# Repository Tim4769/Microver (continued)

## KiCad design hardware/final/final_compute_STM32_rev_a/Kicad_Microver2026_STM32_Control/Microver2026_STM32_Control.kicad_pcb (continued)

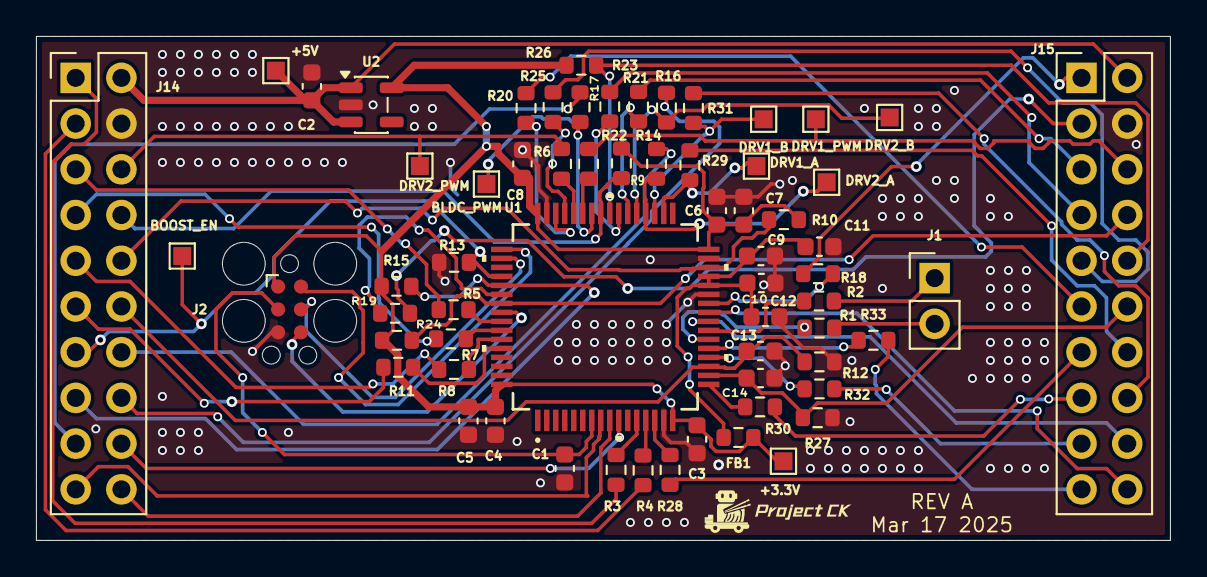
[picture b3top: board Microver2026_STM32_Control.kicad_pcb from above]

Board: 4 copper layers, 63.0 x 28.0 mm, 64 parts (0 on the bottom side), 71 nets.

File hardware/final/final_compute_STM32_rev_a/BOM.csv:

"Reference","Qty","Value","Footprint","JLCPCB part number"
"C1,C3,C4,C5,C7,C9,C11","7","100nF","Capacitor_SMD:C_0603_1608Metric","C14663"
"C2,C6,C8","3","4.7uF","Capacitor_SMD:C_0603_1608Metric","C19666"
"C10,C12","2","1uF","Capacitor_SMD:C_0603_1608Metric","C15849"
"C13,C14","2","10nF","Capacitor_SMD:C_0603_1608Metric","C57112"
"FB1","1","FerriteBead_Small","Resistor_SMD:R_0603_1608Metric","C14709"
"J1","1","Pi URAT","Connector_PinHeader_2.54mm:PinHeader_1x02_P2.54mm_Vertical","C492401"
"J2","1","TC2030","Connector:Tag-Connect_TC2030-IDC-FP_2x03_P1.27mm_Vertical",""
"J14","1","Left","Connector_PinHeader_2.54mm:PinHeader_2x10_P2.54mm_Vertical",""
"J15","1","Right","Connector_PinHeader_2.54mm:PinHeader_2x10_P2.54mm_Vertical",""
"R1,R2,R3,R4,R5,R7,R8,R11,R18,R19,R20,R21,R23,R25,R28,R30,R32,R33","18","100Ω","Resistor_SMD:R_0603_1608Metric","C22775"
"R6,R14,R16,R17,R22,R29,R31","7","1kΩ","Resistor_SMD:R_0603_1608Metric","C21190"
"R9,R10,R15,R24,R26","5","3.3kΩ","Resistor_SMD:R_0603_1608Metric","C22978"
"R12,R27","2","680Ω","Resistor_SMD:R_0603_1608Metric","C23228"
"R13","1","10kΩ","Resistor_SMD:R_0603_1608Metric","C25804"
"TP1","1","+5V","TestPoint:TestPoint_Pad_1.0x1.0mm",""
"TP2","1","+3.3V","TestPoint:TestPoint_Pad_1.0x1.0mm",""
"TP3","1","BLDC_PWM","TestPoint:TestPoint_Pad_1.0x1.0mm",""
"TP4","1","DRV1_A","TestPoint:TestPoint_Pad_1.0x1.0mm",""
"TP5","1","DRV1_B","TestPoint:TestPoint_Pad_1.0x1.0mm",""
"TP6","1","DRV2_A","TestPoint:TestPoint_Pad_1.0x1.0mm",""
"TP7","1","DRV1_PWM","TestPoint:TestPoint_Pad_1.0x1.0mm",""
"TP8","1","DRV2_B","TestPoint:TestPoint_Pad_1.0x1.0mm",""
"TP12","1","DRV2_PWM","TestPoint:TestPoint_Pad_1.0x1.0mm",""
"TP15","1","BOOST_EN","TestPoint:TestPoint_Pad_1.0x1.0mm",""
"U1","1","STM32G473RCT6","STM32_Footprint_Library:LQFP64-10x10mm","C529361"
"U2","1","MIC5365-3.3YD5","Package_TO_SOT_SMD:SOT-23-5","C626098"

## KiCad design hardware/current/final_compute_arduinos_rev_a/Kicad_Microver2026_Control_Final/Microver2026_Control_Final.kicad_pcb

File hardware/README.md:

# Hardware Index

Use this index to avoid opening stale revisions by accident.

## Start here
- `final/README.md` - Latest board revisions (active work only).

## Historical revisions
- `archive/README.md` - Archived revisions and legacy boards.

## Important after folder moves
- KiCad output paths in project files may still point to old folder locations.
- After moving a board revision, update KiCad plot and export paths (Gerber, drill, BOM, CPL) before regenerating manufacturing outputs.

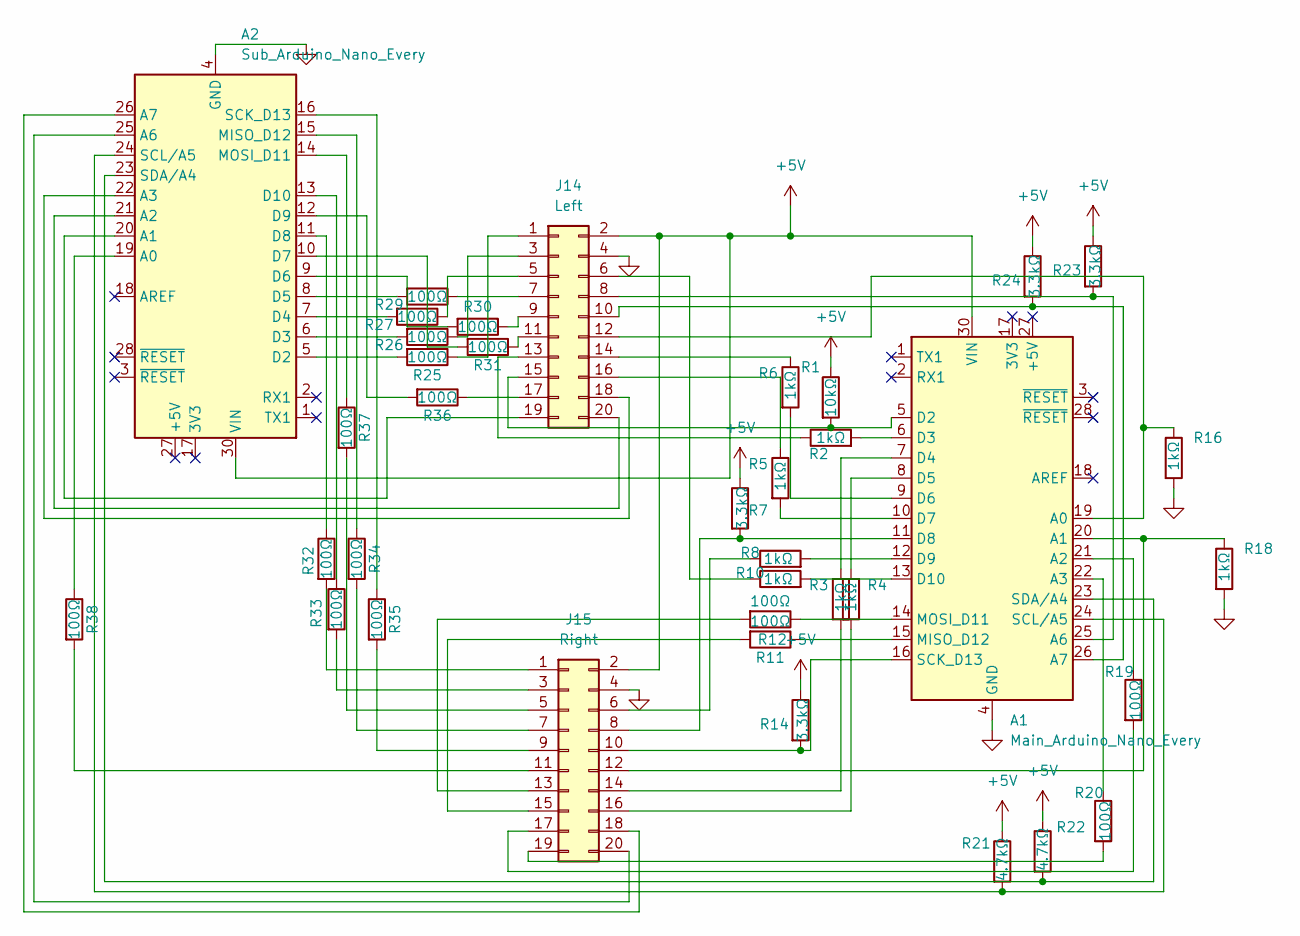
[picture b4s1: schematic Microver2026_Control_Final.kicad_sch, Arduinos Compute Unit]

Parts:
A1: Main_Arduino_Nano_Every; Arduino_Nano
A2: Sub_Arduino_Nano_Every; Arduino_Nano
J14: Left; PinHeader_2x10_P2.54mm_Vertical
J15: Right; PinHeader_2x10_P2.54mm_Vertical
R1: 10kΩ; R_0603_1608Metric; JLCPCB part number C25804
R2, R3, R4, R5, R6, R8, R10, R16, R18: 1kΩ; R_0603_1608Metric; JLCPCB part number C21190
R7, R14, R23, R24: 3.3kΩ; R_0603_1608Metric; JLCPCB part number C22978
R11, R12, R19, R20, R25, R26, R27, R29, R30, R31, R32, R33, R34, R35, R36, R37, R38: 100Ω; R_0603_1608Metric; JLCPCB part number C22775
R21, R22: 4.7kΩ; R_0603_1608Metric; JLCPCB part number C23162

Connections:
+5V: A1.30 (VIN), A2.30 (VIN), J14.2 (Pin_1b), J15.2 (Pin_1b), R1.1, R7.1, R14.1, R21.1, R22.1, R23.1, R24.1
GND: A1.4 (GND), A1.29 (GND), A2.4 (GND), A2.29 (GND), J14.4 (Pin_2b), J15.4 (Pin_2b), R16.2, R18.2
unnamed: A1.19 (A0), J14.12 (Pin_6b), R16.1
unnamed: A1.20 (A1), J15.12 (Pin_6b), R18.1
unnamed: A1.21 (A2), R19.1
unnamed: A1.22 (A3), R20.1
unnamed: A1.25 (A6), J14.8 (Pin_4b), R23.2
unnamed: A1.26 (A7), J14.10 (Pin_5b), R24.2
unnamed: A1.5 (D2), J14.15 (Pin_8a), R1.2
unnamed: A1.6 (D3), R2.2
unnamed: A1.7 (D4), R3.1
unnamed: A1.8 (D5), R4.1
unnamed: A1.9 (D6), R6.2
unnamed: A1.10 (D7), R5.2
unnamed: A1.11 (D8), J15.8 (Pin_4b), R7.2
unnamed: A1.12 (D9), R8.2
unnamed: A1.13 (D10), R10.2
unnamed: A1.15 (MISO_D12), R12.1
unnamed: A1.14 (MOSI_D11), R11.1
unnamed: A1.16 (SCK_D13), J15.10 (Pin_5b), R14.2
unnamed: A1.24 (SCL/A5), A2.24 (SCL/A5), R21.2
unnamed: A1.23 (SDA/A4), A2.23 (SDA/A4), R22.2
unnamed: A2.19 (A0), R38.1
unnamed: A2.20 (A1), J14.19 (Pin_10a)
unnamed: A2.21 (A2), J14.20 (Pin_10b)
unnamed: A2.22 (A3), J14.18 (Pin_9b)
unnamed: A2.25 (A6), J15.20 (Pin_10b)
unnamed: A2.26 (A7), J15.18 (Pin_9b)
unnamed: A2.5 (D2), R25.2
unnamed: A2.6 (D3), R26.2
unnamed: A2.7 (D4), R27.2
unnamed: A2.8 (D5), R29.2
unnamed: A2.9 (D6), R30.2
unnamed: A2.10 (D7), R31.2
unnamed: A2.11 (D8), R32.1
unnamed: A2.12 (D9), R36.2
unnamed: A2.13 (D10), R33.1
unnamed: A2.15 (MISO_D12), R34.1
unnamed: A2.14 (MOSI_D11), R37.1
unnamed: A2.16 (SCK_D13), R35.1
unnamed: J14.1 (Pin_1a), R25.1
unnamed: J14.3 (Pin_2a), R26.1
unnamed: J14.5 (Pin_3a), R27.1
unnamed: J14.6 (Pin_3b), R10.1
unnamed: J14.7 (Pin_4a), R29.1
unnamed: J14.9 (Pin_5a), R30.1
unnamed: J14.11 (Pin_6a), R31.1
unnamed: J14.13 (Pin_7a), R2.1
unnamed: J14.14 (Pin_7b), R6.1
unnamed: J14.16 (Pin_8b), R5.1
unnamed: J14.17 (Pin_9a), R36.1
unnamed: J15.1 (Pin_1a), R32.2
unnamed: J15.3 (Pin_2a), R33.2
unnamed: J15.5 (Pin_3a), R37.2
unnamed: J15.6 (Pin_3b), R8.1
unnamed: J15.7 (Pin_4a), R34.2
unnamed: J15.9 (Pin_5a), R35.2
unnamed: J15.11 (Pin_6a), R38.2
unnamed: J15.13 (Pin_7a), R11.2
unnamed: J15.14 (Pin_7b), R3.2
unnamed: J15.15 (Pin_8a), R12.2
unnamed: J15.16 (Pin_8b), R4.2
unnamed: J15.17 (Pin_9a), R19.2
unnamed: J15.19 (Pin_10a), R20.2

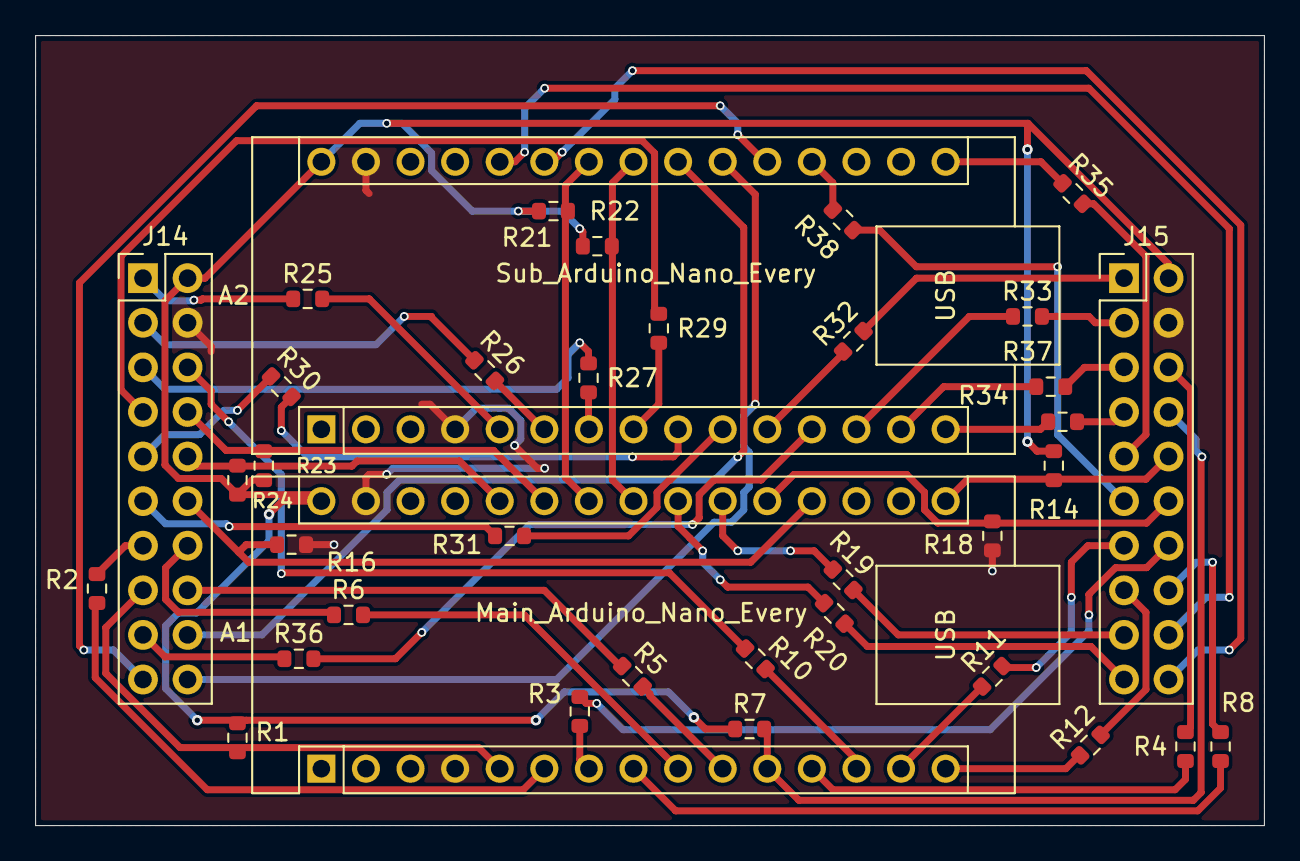
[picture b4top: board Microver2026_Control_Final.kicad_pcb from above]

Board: 4 copper layers, 70.0 x 45.0 mm, 37 parts (0 on the bottom side), 64 nets.

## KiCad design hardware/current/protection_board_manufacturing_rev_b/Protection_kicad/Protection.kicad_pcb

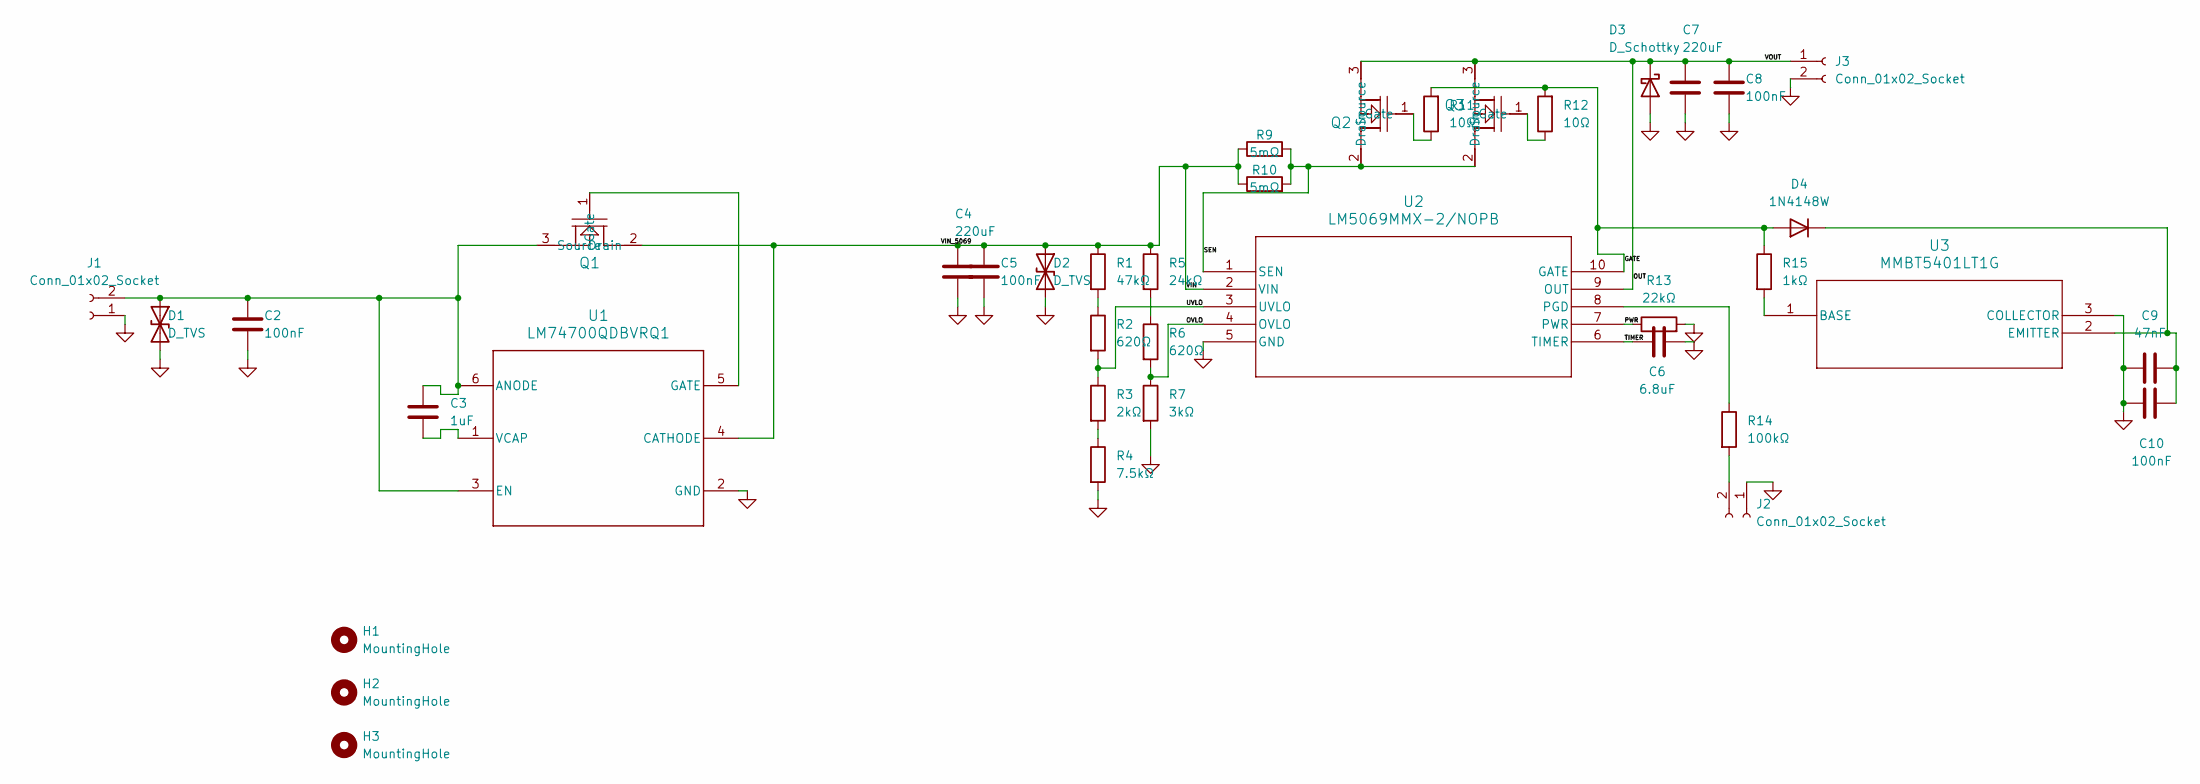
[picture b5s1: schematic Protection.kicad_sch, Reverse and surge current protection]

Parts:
C2, C5, C8, C10: 100nF; C_0603_1608Metric
C3: 1uF; C_0805_2012Metric
C4, C7: 220uF; CP_Radial_D10.0mm_P5.00mm
C6: 6.8uF; C_0603_1608Metric
C9: 47nF; C_0603_1608Metric
D1, D2: D_TVS; D_SMB
D3: D_Schottky; D_SMC
D4: 1N4148W; D_SOD-123
H1, H2, H3: MountingHole; MountingHole_3.2mm_M3
J1, J3: Conn_01x02_Socket; TerminalBlock_MaiXu_MX126-5.0-02P_1x02_P5.00mm
J2: Conn_01x02_Socket; PinHeader_1x02_P2.54mm_Vertical
Q1, Q2, Q3: CSD19536KTT; KTT0002A
R1: 47kΩ; R_0603_1608Metric
R2, R6: 620Ω; R_0603_1608Metric
R3: 2kΩ; R_0603_1608Metric
R4: 7.5kΩ; R_0603_1608Metric
R5: 24kΩ; R_0603_1608Metric
R7: 3kΩ; R_0603_1608Metric
R9, R10: 5mΩ; R_2512_6332Metric
R11, R12: 10Ω; R_0603_1608Metric
R13: 22kΩ; R_0603_1608Metric
R14: 100kΩ; R_0603_1608Metric
R15: 1kΩ; R_0603_1608Metric
U1: LM74700QDBVRQ1; DBV0006A_N
U2: LM5069MMX-2/NOPB; MUB10A
U3: MMBT5401LT1G; SOT-23-3_1P4X3P040_ONS

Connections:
/GATE: D4.2 (A), R11.2, R12.2, R15.1, U2.10 (GATE)
/OUT: C7.1, C8.1, D3.1 (K), J3.1, Q2.3 (Source), Q3.3 (Source), U2.9 (OUT)
/OVLO: R6.2, R7.1, U2.4 (OVLO)
/PWR: R13.1, U2.7 (PWR)
/SEN: Q2.2 (Drain), Q3.2 (Drain), R9.2, R10.2, U2.1 (SEN)
/TIMER: C6.1, U2.6 (TIMER)
/UVLO: R2.2, R3.1, U2.3 (UVLO)
/VIN: C4.1, C5.1, D2.1 (A1), Q1.2 (Drain), R1.1, R5.1, R9.1, R10.1, U1.4 (CATHODE), U2.2 (VIN)
GND: C2.2, C4.2, C5.2, C6.2, C7.2, C8.2, C9.1, C10.1, D1.2 (A2), D2.2 (A2), D3.2 (A), J1.1, J2.1, J3.2, R4.2, R7.2, R13.2, U1.2 (GND), U2.5 (GND), U3.3 (COLLECTOR)
unnamed: C2.1, C3.1, D1.1 (A1), J1.2, Q1.3 (Source), U1.3 (EN), U1.6 (ANODE)
unnamed: C9.2, C10.2, D4.1 (K), U3.2 (EMITTER)
unnamed: J2.2, R14.2
unnamed: Q1.1 (Gate), U1.5 (GATE)
unnamed: Q2.1 (Gate), R11.1
unnamed: Q3.1 (Gate), R12.1
unnamed: R1.2, R2.1
unnamed: R3.2, R4.1
unnamed: R5.2, R6.1
unnamed: C3.2, U1.1 (VCAP)
unnamed: R14.1, U2.8 (PGD)
unnamed: R15.2, U3.1 (BASE)

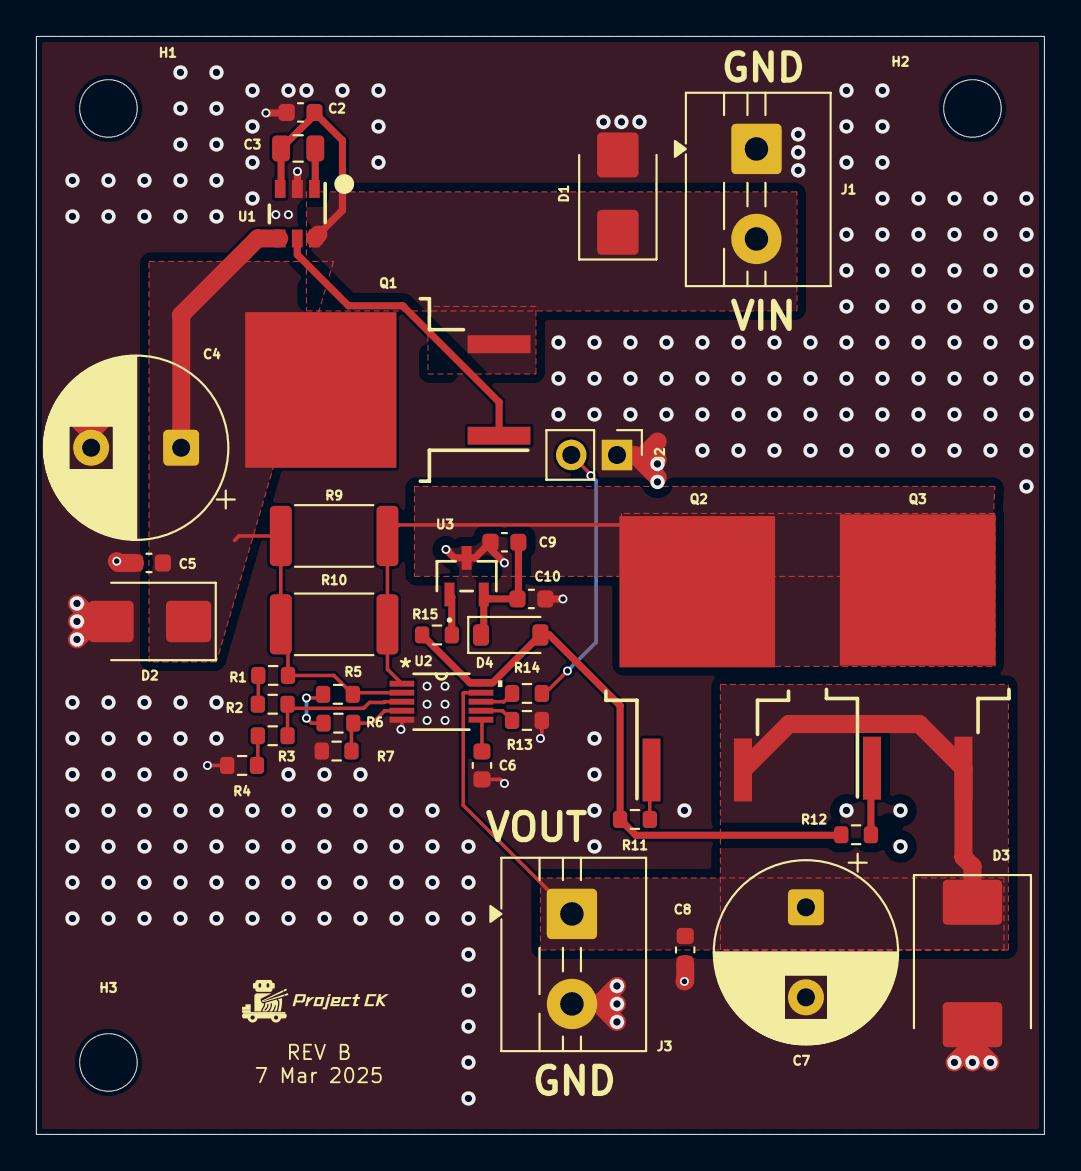
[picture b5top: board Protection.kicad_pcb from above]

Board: 4 copper layers, 56.0 x 61.0 mm, 39 parts (0 on the bottom side), 21 nets.

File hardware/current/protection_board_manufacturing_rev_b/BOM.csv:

"Reference","Qty","Value","Footprint","Datasheet","JPCPCB part number"
"C1,C4,C7","3","220uF","Capacitor_THT:CP_Radial_D10.0mm_P5.00mm","~","C106670"
"C2,C5,C8,C10","4","100nF","Capacitor_SMD:C_0603_1608Metric","~","C14663"
"C3","1","1uF","Capacitor_SMD:C_0805_2012Metric","~","C28323"
"C6","1","6.8uF","Capacitor_SMD:C_0603_1608Metric","~","C338096"
"C9","1","47nF","Capacitor_SMD:C_0603_1608Metric","~","C1622"
"D1,D2","2","D_TVS","Diode_SMD:D_SMB","~","C19077586"
"D3","1","D_Schottky","Diode_SMD:D_SMC","~","C134457"
"D4","1","1N4148W","Diode_SMD:D_SOD-123","https://www.vishay.com/docs/85748/1n4148w.pdf","C7420318"
"J1,J3","2","Conn_01x02_Socket","TerminalBlock:TerminalBlock_MaiXu_MX126-5.0-02P_1x02_P5.00mm","~",""
"J2","1","Conn_01x02_Socket","Connector_PinHeader_2.54mm:PinHeader_1x02_P2.54mm_Vertical","~",""
"Q1,Q2,Q3","3","CSD19536KTT","KTT0002A","https://www.ti.com/lit/gpn/csd19536ktt","C2687963"
"R1","1","47kΩ","Resistor_SMD:R_0603_1608Metric","~","C25819"
"R2,R6","2","620Ω","Resistor_SMD:R_0603_1608Metric","~","C23220"
"R3","1","2kΩ","Resistor_SMD:R_0603_1608Metric","~","C22975"
"R4","1","7.5kΩ","Resistor_SMD:R_0603_1608Metric","~","C23234"
"R5","1","24kΩ","Resistor_SMD:R_0603_1608Metric","~","C23352"
"R7","1","3kΩ","Resistor_SMD:R_0603_1608Metric","~","C4211"
"R8","1","33Ω","Resistor_SMD:R_0603_1608Metric","~","C23140"
"R9,R10","2","5mΩ","Resistor_SMD:R_2512_6332Metric","~","C108931"
"R11,R12","2","10Ω","Resistor_SMD:R_0603_1608Metric","~","C22859"
"R13","1","22kΩ","Resistor_SMD:R_0603_1608Metric","~","C31850"
"R14","1","100kΩ","Resistor_SMD:R_0603_1608Metric","~","C25803"
"R15","1","1kΩ","Resistor_SMD:R_0603_1608Metric","~","C21190"
"U1","1","LM74700QDBVRQ1","DBV0006A_N","https://www.ti.com/lit/gpn/lm74700-q1","C2941042"
"U2","1","LM5069MMX-2/NOPB","MUB10A","https://www.ti.com/lit/gpn/lm5069","C2653582"
"U3","1","MMBT5401LT1G","SOT-23-3_1P4X3P040_ONS","MMBT5401LT1G","C21488"

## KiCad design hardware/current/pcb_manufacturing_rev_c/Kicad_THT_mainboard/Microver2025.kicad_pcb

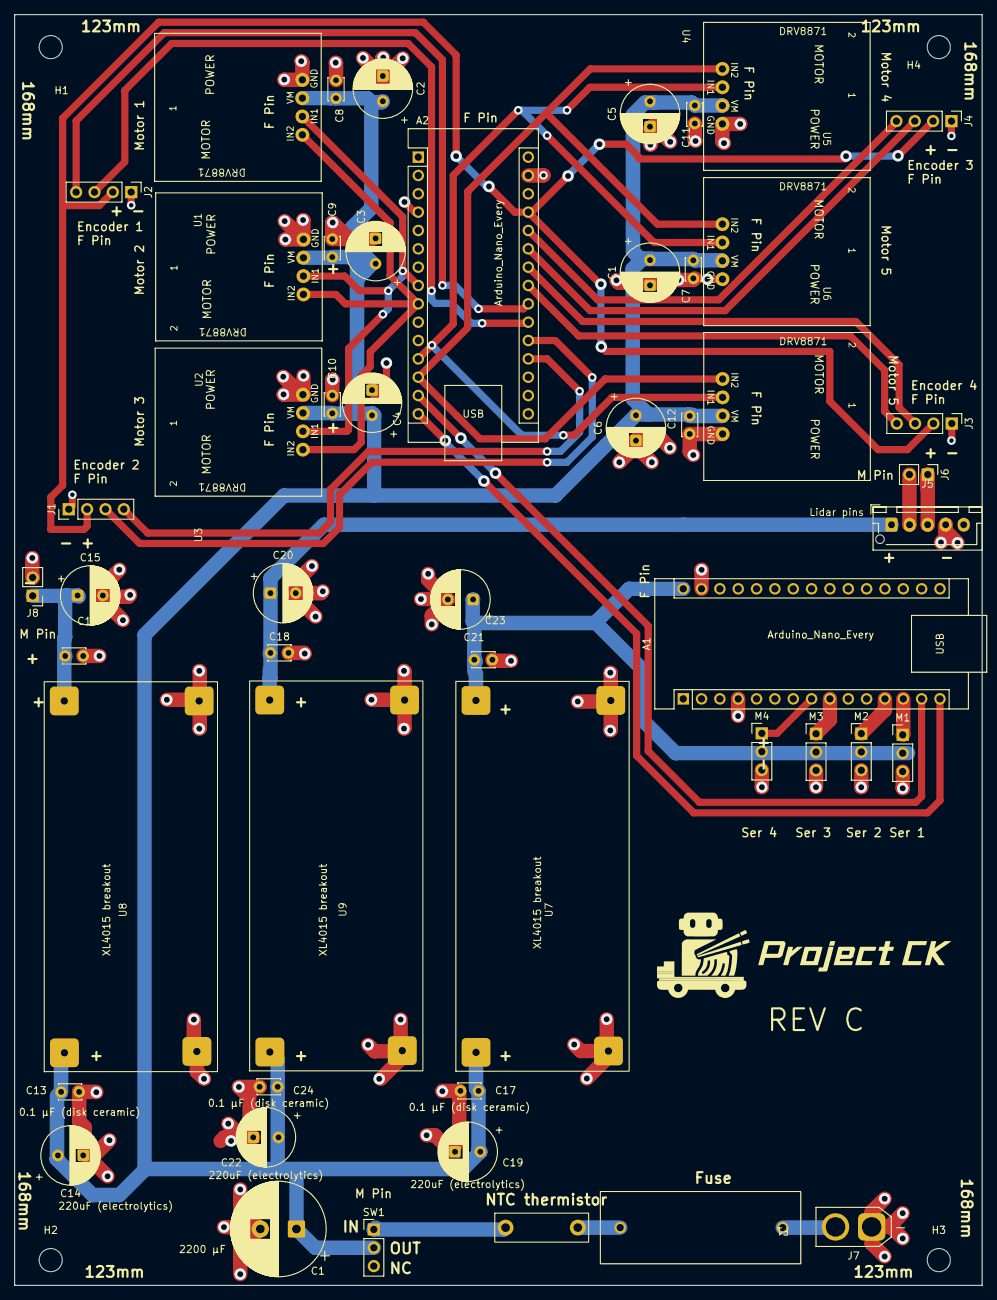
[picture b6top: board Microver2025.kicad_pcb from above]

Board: 4 copper layers, 134.0 x 176.0 mm, 55 parts (0 on the bottom side), 23 nets.

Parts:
A1, A2: Arduino_Nano_Every; Arduino_Nano
C1: 2200 µF; CP_Radial_D13.0mm_P5.00mm
C1#2, C2, C3, C4, C5, C6, C14, C19, C22: 220uF (electrolytics); Marking reversed CP_Radial_D8.0mm_P3.50mm
C7, C8, C9, C10, C11, C12, C13, C16, C17, C18, C23, C24: 0.1 µF (disk ceramic); C_Disc_D3.0mm_W2.0mm_P2.50mm
C15, C20, C21: 220uF (electrolytics); CP_Radial_D8.0mm_P3.50mm
F1: Fuse; Fuse PTF-77
H1, H2, H3, H4: MountingHole; MountingHole_3.2mm_M3
J1, J2, J3, J4: Encoder pins; PinHeader_1x04_P2.54mm_Vertical
J5: Lidar pins; JST_XH_B5B-XH-AM_1x05_P2.50mm_Vertical
J6: Pi 5 TX and RX UART0 (PL011); PinHeader_1x02_P2.54mm_Vertical
J7: Power input connect from battery; AMASS_XT30U-M_1x02_P5.0mm_Vertical
J8: Pi power pins; PinHeader_1x02_P2.54mm_Vertical
M1, M2, M3, M4: Motor_Servo (MG996R); PinHeader_1x03_P2.54mm_Vertical
SW1: SW_SPDT; PinHeader_1x03_P2.54mm_Vertical
TH1: Thermistor_NTC; NTC thermistor Microver
U1, U2, U3, U4, U5, U6: DRV8871_breakout; DRV8871 breakout board
U7, U8, U9: XL4015 breakout; XL4015 breakout board

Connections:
+18V: C1.1, C1#2.2, C2.2, C3.2, C4.2, C5.2, C6.2, C7.2, C8.2, C9.2, C10.2, C11.2, C12.2, C13.2, C14.2, C17.2, C19.2, C22.2, C24.2, F1.1, F1.2, J7.2, SW1.1 (A), SW1.2 (B), TH1.1, TH1.2, U1.4 (VM), U2.4 (VM), U3.4 (VM), U4.4 (VM), U5.4 (VM), U6.4 (VM), U7.1 (IN+), U8.1 (IN+), U9.1 (IN+)
/5V: A1.30 (VIN), A2.27 (+5V), C15.1, C16.1, C18.1, C20.1, C21.1, C23.1, J1.2, J2.2, J3.2, J4.2, J5.1, J8.1, M1.2 (+), M2.2 (+), M3.2 (+), M4.2 (+), U7.3 (OUT+), U8.3 (OUT+), U9.3 (OUT+)
/DIGI_1_1: A2.21 (A2), J2.3
/DIGI_1_2: A2.22 (A3), J2.4
/DIGI_2_1: A2.20 (A1), J1.3
/DIGI_2_2: A2.19 (A0), J1.4
/DIGI_3_1: A2.25 (A6), J4.3
/DIGI_3_2: A2.26 (A7), J4.4
/DIGI_4_1: A2.24 (SCL/A5), J3.3
/DIGI_4_2: A2.23 (SDA/A4), J3.4
/PWM_M1_1: A2.8 (D5), U1.3 (IN1), U2.3 (IN1), U3.3 (IN1)
/PWM_M1_2: A2.9 (D6), U1.2 (IN2), U2.2 (IN2), U3.2 (IN2)
/PWM_M4_1: A2.12 (D9), U4.3 (IN1), U5.3 (IN1), U6.3 (IN1)
/PWM_M4_2: A2.13 (D10), U4.2 (IN2), U5.2 (IN2), U6.2 (IN2)
/PWM_SER1: A1.13 (D10), M1.1 (PWM)
/PWM_SER2: A1.12 (D9), M2.1 (PWM)
/PWM_SER3: A1.9 (D6), M3.1 (PWM)
/PWM_SER4: A1.8 (D5), M4.1 (PWM)
/URAT_MI: A1.14 (MOSI), A2.14 (MOSI)
/URAT_MO: A1.15 (MISO), A2.15 (MISO)
/URAT_PI_1: J5.3, J6.1
/URAT_PI_2: J5.2, J6.2
GND: A1.4 (GND), A1.29 (GND), A2.4 (GND), A2.29 (GND), C1.2, C1#2.1, C2.1, C3.1, C4.1, C5.1, C6.1, C7.1, C8.1, C9.1, C10.1, C11.1, C12.1, C13.1, C14.1, C15.2, C16.2, C17.1, C18.2, C19.1, C20.2, C21.2, C22.1, C23.2, C24.1, J1.1, J2.1, J3.1, J4.1, J5.4, J7.1, J8.2, M1.3 (-), M2.3 (-), M3.3 (-), M4.3 (-), U1.1 (GND), U2.1 (GND), U3.1 (GND), U4.1 (GND), U5.1 (GND), U6.1 (GND), U7.2 (IN-), U7.4 (OUT-), U8.2 (IN-), U8.4 (OUT-), U9.2 (IN-), U9.4 (OUT-)

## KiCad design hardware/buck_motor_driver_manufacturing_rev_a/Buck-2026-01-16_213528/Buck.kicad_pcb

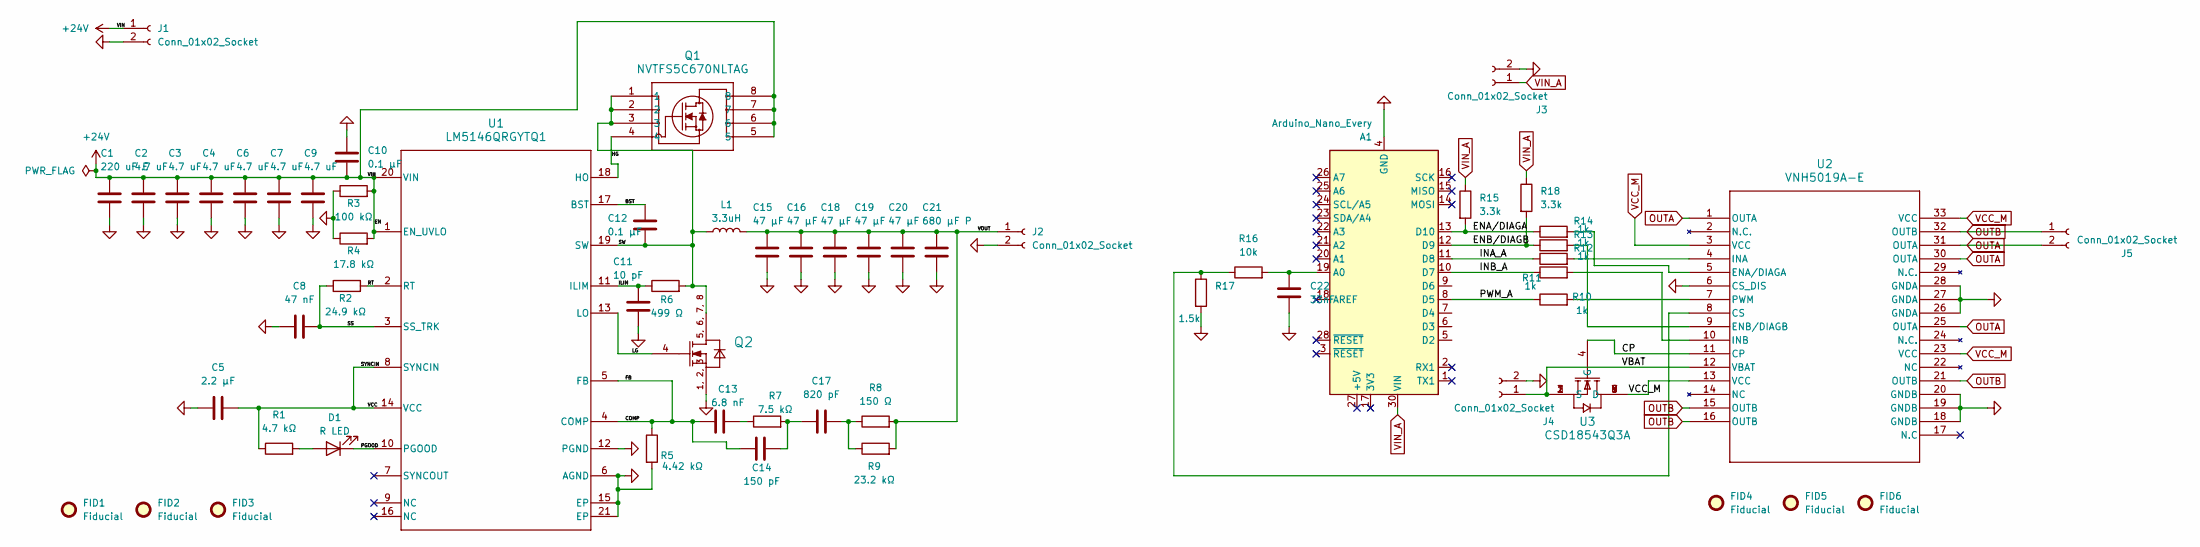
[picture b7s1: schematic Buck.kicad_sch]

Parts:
A1: Arduino_Nano_Every; Arduino_Nano
C1: 220 uF E; CP_Elec_4x5.4; JLCPCB Part Number C116389
C2, C3, C4, C6, C7, C9: 4.7 uF; C_1206_3216Metric; JLCPCB Part Number C51205
C5: 2.2 μF; C_0603_1608Metric; JLCPCB Part Number C43922
C8: 47 nF; C_0402_1005Metric; JLCPCB Part Number C307434
C10, C12: 0.1 μF; C_0603_1608Metric; JLCPCB Part Number C14663
C11: 10 pF; C_0402_1005Metric; JLCPCB Part Number C1845716
C13: 6.8 nF; C_0603_1608Metric; JLCPCB Part Number C107097
C14: 150 pF; C_0603_1608Metric; JLCPCB Part Number C1594
C15, C16, C18, C19, C20: 47 μF; C_1210_3225Metric; JLCPCB Part Number C5440143
C17: 820 pF; C_0603_1608Metric; JLCPCB Part Number C1632
C21: 680 µF P; MA35V680M10X13; JLCPCB Part Number C48971043
C22: 33nF; C_0603_1608Metric; JLCPCB Part Number C21117
D1: R LED; LED_0402_1005Metric; JLCPCB Part Number C510301
FID1, FID2, FID3, FID4, FID5, FID6: Fiducial; Fiducial_1mm_Mask2mm
J1, J2, J3, J4, J5: Conn_01x02_Socket; TerminalBlock_MaiXu_MX126-5.0-02P_1x02_P5.00mm; JLCPCB Part Number C8269
L1: 3.3uH; MS1770-3R3M; JLCPCB Part Number C18337521
Q1: NVTFS5C670NLTAG; WDFN8_511AB_ONS; JLCPCB Part Number C900529
Q2: BSC014N06NS; INF-PG-TDSON-8-FL; ManufacturerPartNumber BSC014N06NS; JLCPCB Part Number C113391
R1: 4.7 kΩ; R_0402_1005Metric; JLCPCB Part Number C25900
R2: 24.9 kΩ; R_0603_1608Metric; JLCPCB Part Number C25962
R3: 100 kΩ; R_0603_1608Metric; JLCPCB Part Number C25803
R4: 17.8 kΩ; R_0603_1608Metric; JLCPCB Part Number C2933161
R5: 4.42 kΩ; R_0805_2012Metric; JLCPCB Part Number C2960870
R6: 499 Ω; R_0603_1608Metric; JLCPCB Part Number C23065
R7: 7.5 kΩ; R_0603_1608Metric; JLCPCB Part Number C23234
R8: 150 Ω; R_0603_1608Metric; JLCPCB Part Number C22808
R9: 23.2 kΩ; R_0603_1608Metric; JLCPCB Part Number C23346
R10, R11, R12, R13, R14: 1k; R_0603_1608Metric; JLCPCB Part Number C21190
R15, R18: 3.3k; R_0603_1608Metric; JLCPCB Part Number C22978
R16: 10k; R_0603_1608Metric; JLCPCB Part Number C25804
R17: 1.5k; R_0603_1608Metric; JLCPCB Part Number C22843
U1: LM5146QRGYTQ1; RGY0020B; JLCPCB Part Number C2876733
U2: VNH5019A-E; SOIC_5019A-E_STM; JLCPCB Part Number C2653552
U3: CSD18543Q3A; DNH0008A; JLCPCB Part Number C840100

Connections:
+24V: C1.1, C2.1, C3.1, C4.1, C6.1, C7.1, C9.1, C10.2, J1.1, Q1.5, Q1.6, Q1.7, Q1.8, R3.2, R4.2, U1.1 (EN_UVLO), U1.20 (VIN)
/BST: C12.1, U1.17 (BST)
/COMP: C13.1, C14.1, R5.1, U1.4 (COMP), U1.5 (FB)
/CP: U2.11 (CP), U3.4 (G)
/ENA/DIAGA: A1.13 (D10), R14.1, R15.2
/ENB/DIAGB: A1.12 (D9), R13.1, R18.2
/HG: Q1.4, U1.18 (HO)
/ILIM: C11.1, R6.1, U1.11 (ILIM)
/INA_A: A1.11 (D8), R12.1
/INB_A: A1.10 (D7), R11.1
/LG: Q2.4 (GATE), U1.13 (LO)
/PGOOD: D1.1 (K), U1.10 (PGOOD)
/PWM_A: A1.8 (D5), R10.1
/RT: R2.2, U1.2 (RT)
/SS: C8.2, R2.1, U1.3 (SS_TRK)
/SW: C12.2, L1.1, Q1.1, Q1.2, Q1.3, Q2.5 (DRAIN), Q2.6 (DRAIN), Q2.7 (DRAIN), Q2.8 (DRAIN), R6.2, U1.19 (SW)
/SYNCIN: C5.2, R1.1, U1.8 (SYNCIN), U1.14 (VCC)
/VBAT: J4.1, U2.12 (VBAT), U3.1 (S), U3.2 (S), U3.3 (S)
/VOUT: C15.1, C16.1, C18.1, C19.1, C20.1, C21.1, J2.1, L1.2, R8.2, R9.2
GND: A1.4 (GND), A1.29 (GND), C1.2, C2.2, C3.2, C4.2, C5.1, C6.2, C7.2, C8.1, C9.2, C10.1, C11.2, C15.2, C16.2, C18.2, C19.2, C20.2, C21.2, C22.2, J1.2, J2.2, J3.2, J4.2, Q2.1 (SOURCE), Q2.2 (SOURCE), Q2.3 (SOURCE), R3.1, R4.1, R5.2, R17.2, U1.6 (AGND), U1.12 (PGND), U1.15 (EP), U1.21 (EP), U1.V, U2.6 (CS_DIS), U2.18 (GNDB), U2.19 (GNDB), U2.20 (GNDB), U2.26 (GNDA), U2.27 (GNDA), U2.28 (GNDA)
unnamed: A1.19 (A0), C22.1, R16.2
unnamed: C13.2, R7.1
unnamed: C14.2, C17.1, R7.2
unnamed: C17.2, R8.1, R9.1
unnamed: D1.2 (A), R1.2
unnamed: R16.1, R17.1, U2.8 (CS)
unnamed: R14.2, U2.5 (ENA/DIAGA)
unnamed: R13.2, U2.9 (ENB/DIAGB)
unnamed: R12.2, U2.4 (INA)
unnamed: R11.2, U2.10 (INB)
unnamed: R10.2, U2.7 (PWM)
OUTA: J5.2, U2.1 (OUTA), U2.25 (OUTA), U2.30 (OUTA), U2.31 (OUTA)
OUTB: J5.1, U2.15 (OUTB), U2.16 (OUTB), U2.21 (OUTB), U2.32 (OUTB)
VCC_M: U2.3 (VCC), U2.13 (VCC), U2.23 (VCC), U2.33 (VCC), U3.5 (D), U3.6 (D), U3.7 (D), U3.8 (D), U3.9 (D), U3.V
VIN_A: A1.30 (VIN), J3.1, R15.1, R18.1

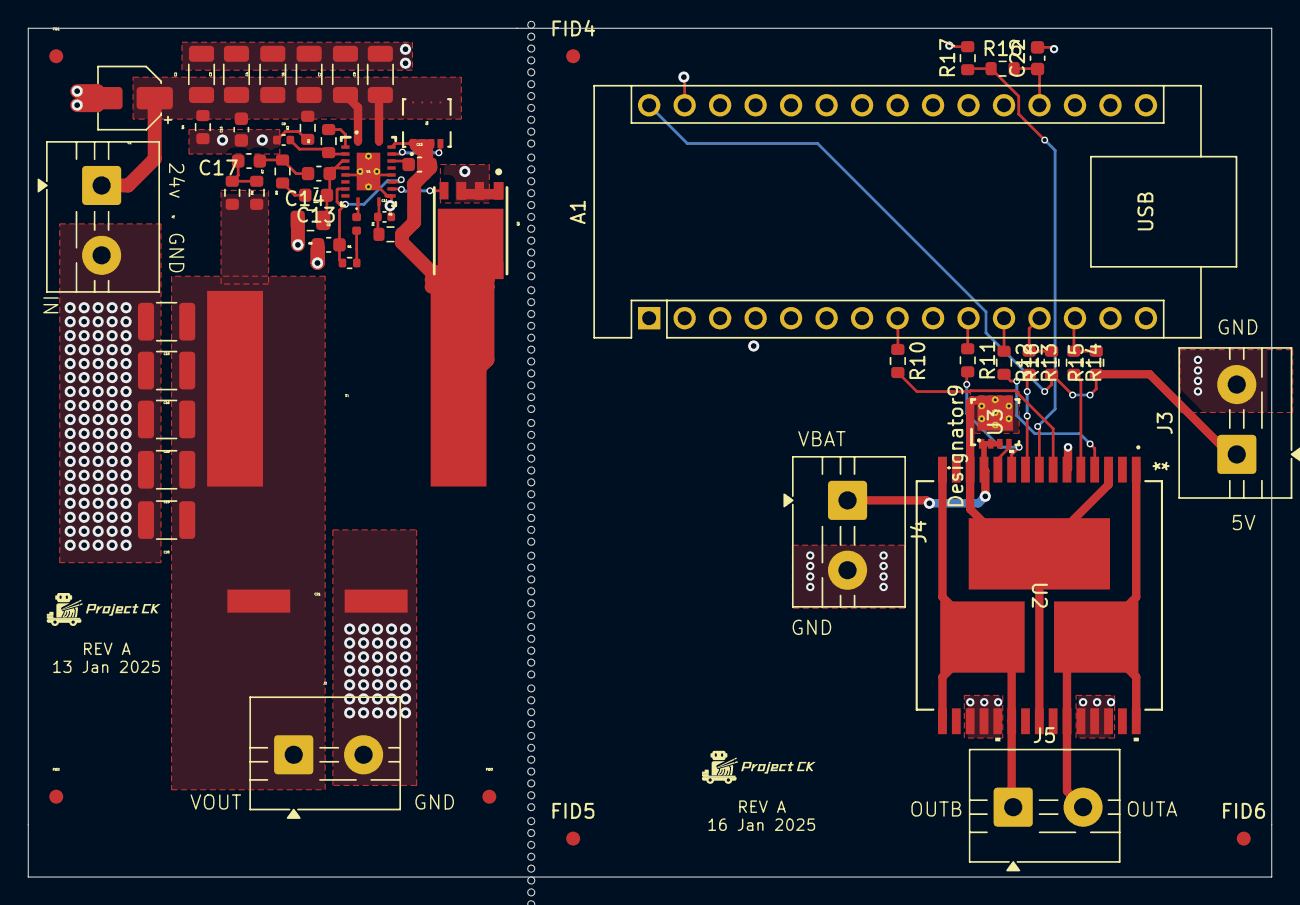
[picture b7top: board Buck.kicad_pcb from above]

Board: 4 copper layers, 89.0 x 60.8 mm, 59 parts (0 on the bottom side), 35 nets.

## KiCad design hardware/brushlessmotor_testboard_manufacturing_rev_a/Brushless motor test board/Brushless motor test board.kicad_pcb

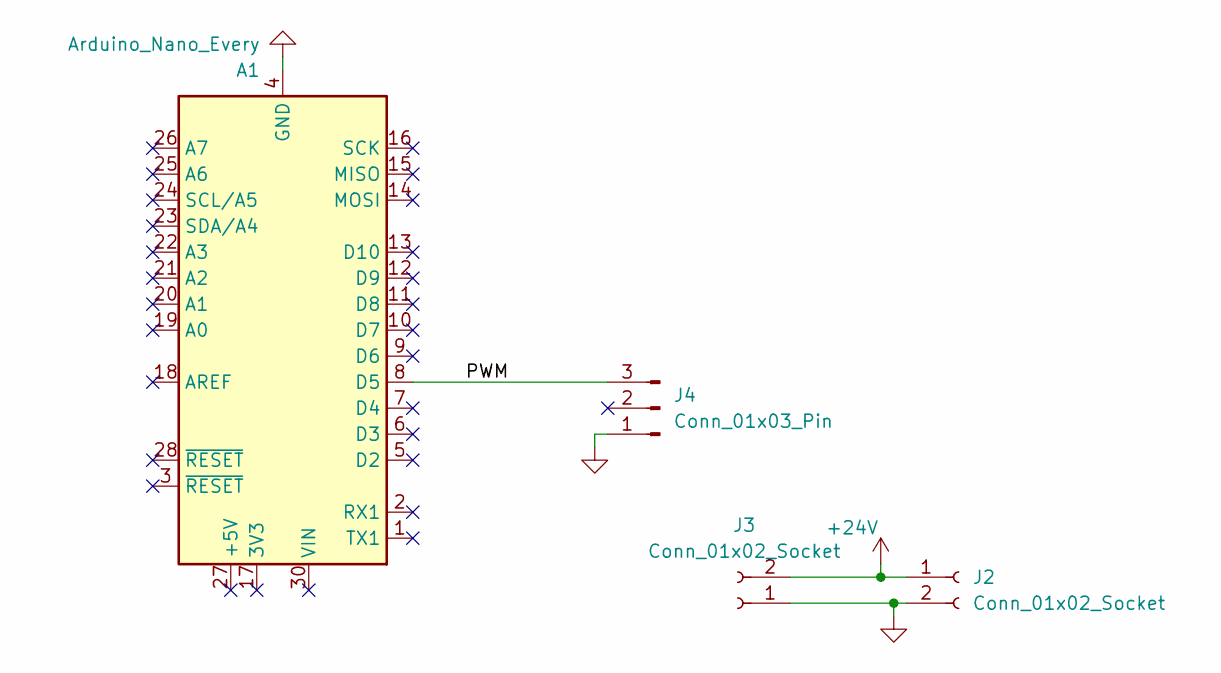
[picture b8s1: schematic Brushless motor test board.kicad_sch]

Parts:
A1: Arduino_Nano_Every; Arduino_Nano
J2, J3: Conn_01x02_Socket; TerminalBlock_MaiXu_MX126-5.0-02P_1x02_P5.00mm
J4: Conn_01x03_Pin; PinHeader_1x03_P2.54mm_Vertical

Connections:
+24V: J2.1, J3.2
/PWM: A1.8 (D5), J4.3
GND: A1.4 (GND), A1.29 (GND), J2.2, J3.1, J4.1

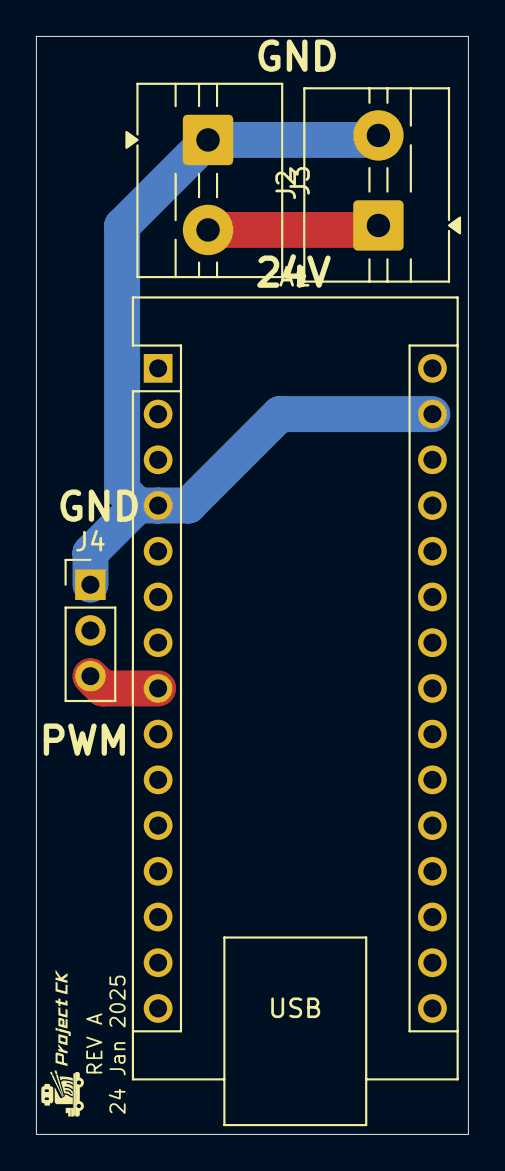
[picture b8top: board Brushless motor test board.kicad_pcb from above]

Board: 2 copper layers, 24.0 x 61.0 mm, 4 parts (0 on the bottom side), 3 nets.

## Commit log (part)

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2025-02-02 Files for Raspberry Pi and Arduino added
2025-02-02 Rename Rasberry pi code.py to Raspberry pi code.py
2025-06-03 Add delay in interrupt listener to reduce CPU usage
2026-01-05 Initial import of Microver project files
2026-01-05 Remove duplicate root code and refresh README
2026-01-05 Reorganize top-level folders
2026-01-05 Refresh README layout description
2026-01-15 Add focused motor, encoder, and servo diagnostics
2026-01-30 Align naming, licensing, and cleanup
    - rename hardware/archive/assets folders to underscore style and move fab outputs accordingly\n- add explicit LICENSE, update README with repo map and license pointers\n- drop Finder .DS_Store files 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
2026-01-30 Document license files in repo map
    - list LICENSE alongside NOTICE in the top-level map so newcomers find terms quickly\n- clarify that reuse requires prior permission
2026-02-10 Add buck/boost rev B releases and refresh power docs
    - Document Standard Component Finder GPT utility.
    - Import boost converter Rev A/B KiCad projects, backups, bench PDFs/XLSX, and generated BOM/CPL/Gerbers; expand Rev B README with updated date, stack-up, value corrections, and EMI via shielding.
    - Add buck-only Rev B KiCad project/backups plus calculator, manufacturing files, README, and test procedure; retire motor-driver Rev B docs in favor of the buck-only spin.
    - Capture buck motor driver Rev A erratum, relocate motor_driver_test sketch into a dedicated folder, and add the KiCad snapshot/behavior log.
    - Refresh top-level README wording to point to the buck-only Rev B and update de
2026-02-12 hardware: refresh boost rev b outputs and add LM5050 OR-ing rev a package
    Update Boost Converter Rev B design/manufacturing files and add a new LM5050 OR-ing manufacturing package with standardized documentation.
    Boost Rev B:
    - Updated KiCad source files (.kicad_sch/.kicad_pcb/.kicad_prl), symbol libraries, footprint library entries, and fp cache.
    - Added MCU-controlled shutdown path by pulling LM5122 SS low via MOSFET.
    - Kept UVLO path for threshold function (not used for shutdown), so each re-enable triggers a fresh soft-start ramp from SS release.
    - Regenerated manufacturing artifacts: BOM, CPL, Gerbers, drill files, Gerber job, and Gerber.zip.
2026-02-12 hardware: add buck+motor driver rev a KiCad backup (2026-02-12_092032)
2026-02-22 repo: reorganize firmware layout and add current/archive hardware navigation
    This commit consolidates documentation + repository organization work so contributors
    land on active board revisions by default while preserving existing KiCad project
    paths and historical traceability.
    Hardware navigation and revision focus
    - Add a top-level hardware index at `hardware/README.md`.
    - Introduce `hardware/current/` as the canonical "start here" navigation layer
2026-02-22 docs: simplify current status to latest board revisions
2026-02-22 refactor(hardware): move board revisions into current/archive
    Physically relocates board revision folders under hardware/current and hardware/archive, removes old pointer-only helper folders, and updates top-level hardware navigation docs and links to the new r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
2026-02-22 chore: ignore and clean macOS .DS_Store files
2026-02-22 docs: simplify board READMEs by removing planned/action sections
2026-02-24 Reorganize KiCad hardware folders and add protection board project
2026-03-07 docs(hardware): add 2026-03-07 layout updates for current power boards
2026-03-07 hardware(pcb): update current Protection/Boost/Buck/ORing board files
2026-03-07 hardware(pcb): update buck motor driver kicad files
2026-04-05 Update hardware releases and simplify test procedures
2026-04-14 Reorganize hardware folders and refresh docs
2026-05-08 added flow charts, jingle, and mechanical folder
2026-05-08 added placeholder for mechanical folder
2026-05-08 Document project structure and add photos
2026-05-08 Update Microver documentation
2026-05-09 added components stl to mechanical folder
2026-05-10 added all step files for components and assemblies
2026-05-10 trying to add step files again
2026-05-10 added a readme for the mechanical section
2026-05-10 Pushing code
2026-05-10 Revert "yes"
    This reverts commit f8345206c5218b45d5793c997aefd75b5dfbe200.
2026-05-10 Revert "yes"
    This reverts commit 0604e4e4b57cd52e776e62b66b58274557493423.
2026-05-10 pushed code
2026-05-10 Organize rover documentation and hardware assets
2026-05-11 Update README rover photo
2026-05-28 Update vulnerable Python dependencies
